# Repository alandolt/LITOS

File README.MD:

# LITOS - **L**ed **I**llumination **T**ool for **O**ptogenetic **S**timulation

**For more information or if you need any help, please contact us at litosforscience[at]outlook.com.**

The **L**ed **I**llumination **T**ool for **O**ptogenetic **S**timulation (**LITOS**) can be used for the stimulation of cells containing an optogenetic system. A commercially available 32x64 RGB LED matrix is used to illuminate cells placed in various microplate formats (6 well up to 96 wells), petri dishes or cell culture flasks. The control unit for the LED matrix is a custom-built printed circuit board (PCB) containing a screen which shows relevant information during the illumination process. 

During LITOS development, we deliberately focused on user-friendliness. LITOS can be ordered pre-built, thus no complicated assembly process is required. Individual stimulation patterns can be first created in a spreadsheet application, like Microsoft Excel, then they are loaded to LITOS over an easy-to-use interface, accessible as a website hosted on the device itself. Thus, no knowledge of a programming language is needed, and the device can even be operated by nontechnical oriented users. 

*LITOS, an easy-to-use system for optogenetic stimulation*

## Why another device for optogenetic stimulation
Optogenetic methods are powerful tools to assess complex signalling pathways with a high spatial-temporal resolution. However, there is a lack of adequate instrumentation to exploit these methods allowing high-throughput automated experiments. While available commercial devices are often too expensive, published solutions requires programming knowledge or have a complicated assembly process. We presents therefore LITOS, a new emerging tool to render optogenetic methods even accessible to labs with a small budget or non-technical user. Thanks to the easy-to-use–interface no knowledge of a programming language is needed, whereas it is still possible to program complex stimulation patterns. Despite being delivered pre-assembled, LITOS remains significantly cheaper than most of the published and commercially available solutions, costing only $ 150. By using a LED matrix as illumination source, even petri-dishes or cell culture flasks can be stimulated in addition to different formats of microtiter plates.

## Features 
- Easy-to-use graphical user interface to change stimulation patterns for optogenetic experiments. No programming knowledge is required. 
- Stimulation patterns are provided as spreadsheet files (MS Excel, LibreOffice Calc)
- It comes pre-assembled. Neither a 3D printer, nor soldering are required before you can start your experiments. 
- Cells can be placed in well plates (96, 48, 24, 12), petri dishes, or cell culture flasks. 
- Very affordable, only about $150 per device. 

## Getting started

To learn more about LITOS, please read our [paper, published 2022 in scientific reports](https://www.nature.com/articles/s41598-022-17312-x), consult our [github wiki](../../wiki) or checkout the [LITOS - First steps](https://youtu.be/o76gi3OUZvs) video.

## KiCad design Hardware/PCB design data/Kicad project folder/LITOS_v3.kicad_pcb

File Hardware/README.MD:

# LITOS Hardware
In case you want to order LITOS directly from a PCB manufacturing service, the folder [*PCB design data*](PCB%20design%20data) contains the needed information (Gerbers file with PCB position file, schematics, and bill of material). Additionally, you can find the raw KiCad PCB layout project under [*LITOS Kicad Rev4.3.zip*](PCB%20design%20data/LITOS%20Kicad%20Rev4.3.zip). 

For the proper alignment of the microtiter plate on the LED matrix the blueprints (for building them with a 3D printer or a CNC machine) for two different masks (one / two microplates) are provided under [*Alignment masks*](Alignment%20masks). The mask for one microplate allows its placement in the middle of the LED matrix, whereas the mask for two plates stocks them horizontally. This allows to stimulate two multiwell plates with one LITOS to further increase through-put. Please note that when using the mask for two plates, the first and last row cannot be illuminated. 

An optional 3D printed case that protects LITOS can be found in the [*3D printed case*](3D%20printed%20case) folder. The case comes in two versions, with or without ventilation holes. Albeit, given that LITOS does not heat up excessively, you can use whichever version you prefer. To minimize overhangs, we recommend you print the case in the orientation it is stored in the .stl file, the open side of the case facing the printer plate. To adjust for under- or overextruding printers, changing the scale of the whole design worked well for us (98%-102%). No support structures were needed with our printer (Creality CR 20 Pro).

<br>

> **Warning** By default, the source code adapted for revision 4 is used during the programming process. When you are still using an older revision 3 board, you can choose the adapted source code for this version by selecting LITOS_Rev2_Rev3 as build environment in PlatformIO. 

*Chose the build environment LITOS_Rev2_Rev3 when you still use an old Rev2 or Rev3 LITOS, else you can directly choose LITOS as build environment.*

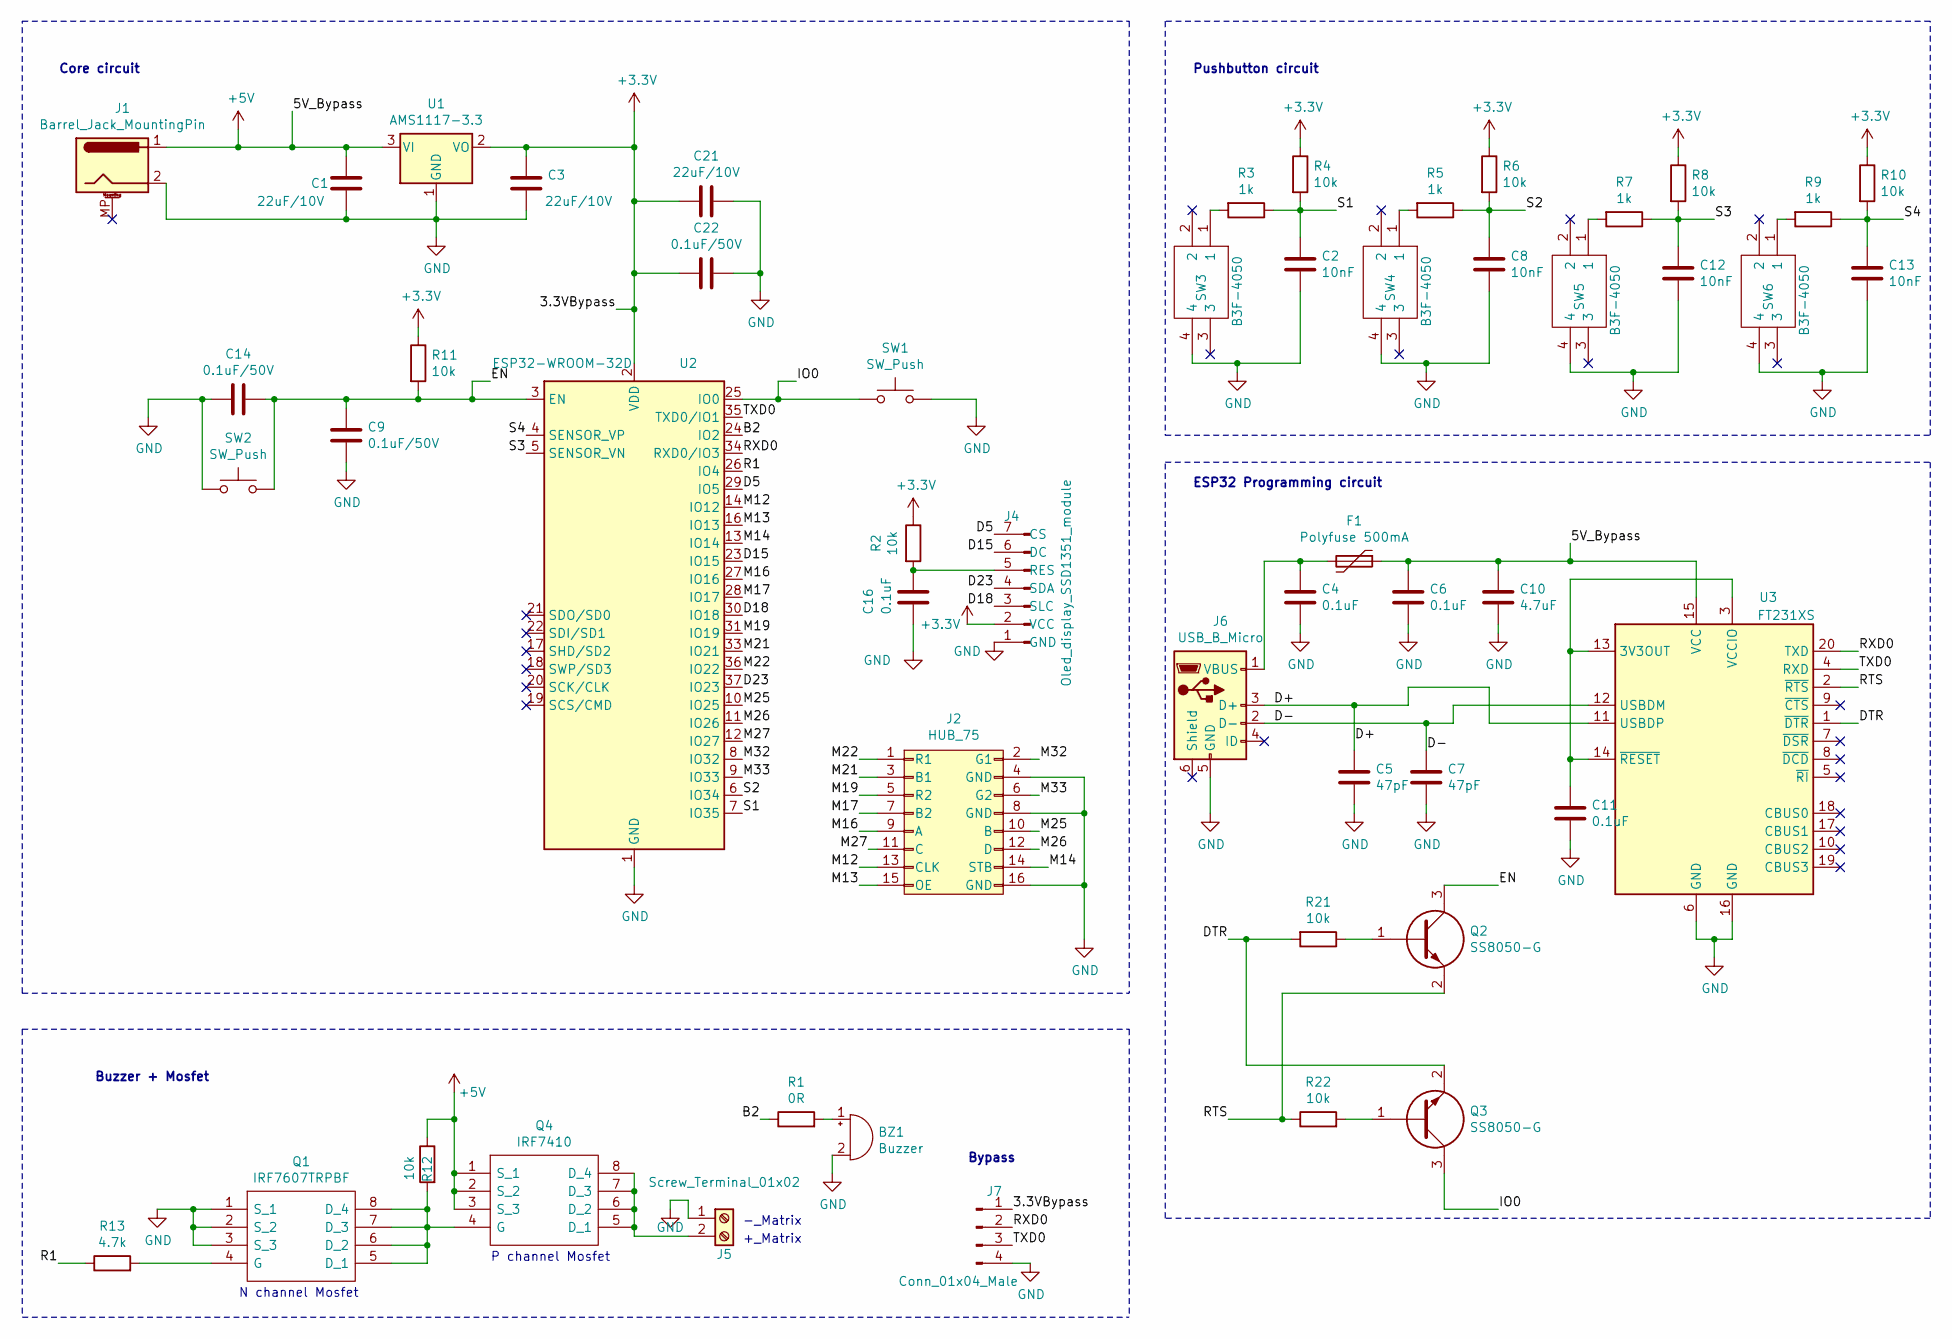
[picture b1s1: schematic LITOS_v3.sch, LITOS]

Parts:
BZ1: Buzzer; CEM-1203_42_
C1, C3, C21: 22uF/10V; C_0603_1608Metric_Pad1.05x0.95mm_HandSolder
C2, C8, C12, C13: 10nF; C_0603_1608Metric_Pad1.05x0.95mm_HandSolder
C4, C6, C11, C16: 0.1uF; C_0603_1608Metric_Pad1.05x0.95mm_HandSolder
C5, C7: 47pF; C_0603_1608Metric_Pad1.05x0.95mm_HandSolder
C9, C14, C22: 0.1uF/50V; C_0603_1608Metric_Pad1.05x0.95mm_HandSolder
C10: 4.7uF; C_0603_1608Metric_Pad1.05x0.95mm_HandSolder
F1: Polyfuse 500mA; Fuse_0805_2012Metric_Pad1.15x1.40mm_HandSolder
J1: Barrel_Jack_MountingPin; CONSOCJ2155
J2: HUB_75; DIPS254W75P254L2764H991Q16N
J4: Oled_display_SSD1351_module; PinSocket_1x07_P2.54mm_Vertical
J5: Screw_Terminal_01x02; SHDR2W100P0X500_1X2_1000X760X1040P
J6: USB_B_Micro; 101181930001LF
J7: Conn_01x04_Male; PinHeader_1x04_P2.54mm_Vertical
Q1: IRF7607TRPBF; SOP65P490X111-8N; Manufacturer_Part_Number IRF7607TRPBF
Q2, Q3: SS8050-G; SOT95P240X115-3N; Mouser Part Number 750-SS8050-G
Q4: IRF7410; SOIC127P600X175-8N
R1: 0R; R_0603_1608Metric_Pad1.05x0.95mm_HandSolder
R2, R4, R6, R8, R10, R11, R12, R21, R22: 10k; R_0603_1608Metric_Pad1.05x0.95mm_HandSolder
R3, R5, R7, R9: 1k; R_0603_1608Metric_Pad1.05x0.95mm_HandSolder
R13: 4.7k; R_0603_1608Metric_Pad1.05x0.95mm_HandSolder
SW1, SW2: SW_Push; PTS647SM70SMTR2LFS
SW3, SW4, SW5, SW6: B3F-4050; B3F-4000; Mouser Part Number 653-B3F-4050
U1: AMS1117-3.3; SOT-223-3_TabPin2
U2: ESP32-WROOM-32D; ESP32-WROOM-32
U3: FT231XS; SSOP-20_3.9x8.7mm_P0.635mm

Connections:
+3V3: C3.1, C21.2, C22.2, J4.2 (VCC), J7.1, R2.1, R4.1, R6.1, R8.1, R10.1, R11.1, U1.2 (VO), U2.2 (VDD)
+5V: C1.1, C6.2, C10.1, F1.1, J1.1, Q4.1 (S_1), Q4.2 (S_2), Q4.3 (S_3), R12.1, U1.3 (VI), U3.15 (VCC)
/B2: R1.1, U2.24 (IO2)
/D5: J4.7 (CS), U2.29 (IO5)
/D15: J4.6 (DC), U2.23 (IO15)
/D18: J4.3 (SLC), U2.30 (IO18)
/D23: J4.4 (SDA), U2.37 (IO23)
/D+: C5.1, J6.3 (D+), U3.11 (USBDP)
/D-: C7.1, J6.2 (D-), U3.12 (USBDM)
/DTR: Q3.2, R21.2, U3.1 (~DTR)
/EN: C9.1, C14.1, Q2.3, R11.2, SW2.2, U2.3 (EN)
/IO0: Q3.3, SW1.1, U2.25 (IO0)
/M12: J2.13 (CLK), U2.14 (IO12)
/M13: J2.15 (OE), U2.16 (IO13)
/M14: J2.14 (STB), U2.13 (IO14)
/M16: J2.9 (A), U2.27 (IO16)
/M17: J2.7 (B2), U2.28 (IO17)
/M19: J2.5 (R2), U2.31 (IO19)
/M21: J2.3 (B1), U2.33 (IO21)
/M22: J2.1 (R1), U2.36 (IO22)
/M25: J2.10 (B), U2.10 (IO25)
/M26: J2.12 (D), U2.11 (IO26)
/M27: J2.11 (C), U2.12 (IO27)
/M32: J2.2 (G1), U2.8 (IO32)
/M33: J2.6 (G2), U2.9 (IO33)
/R1: R13.1, U2.26 (IO4)
/RTS: Q2.2, R22.1, U3.2 (~RTS)
/RXD0: J7.2, U2.34 (RXD0/IO3), U3.20 (TXD)
/S1: C2.2, R3.1, R4.2, U2.7 (IO35)
/S2: C8.2, R5.1, R6.2, U2.6 (IO34)
/S3: C12.2, R7.1, R8.2, U2.5 (SENSOR_VN)
/S4: C13.2, R9.1, R10.2, U2.4 (SENSOR_VP)
/TXD0: J7.3, U2.35 (TXD0/IO1), U3.4 (RXD)
GND: BZ1.2 (+), C1.2, C2.1, C3.2, C4.2, C5.2, C6.1, C7.2, C8.1, C9.2, C10.2, C11.2, C12.1, C13.1, C14.2, C16.2, C21.1, C22.1, J1.2, J2.4 (GND), J2.8 (GND), J2.16 (GND), J4.1 (GND), J5.1, J6.5 (GND), J7.4, Q1.1 (S_1), Q1.2 (S_2), Q1.3 (S_3), SW1.2, SW2.1, SW3.4, SW4.4, SW5.4, SW6.4, U1.1 (GND), U2.1 (GND), U2.15 (GND), U2.38 (GND), U2.39 (GND), U3.6 (GND), U3.16 (GND)
unnamed: BZ1.1 (-), R1.2
unnamed: C4.1, F1.2, J6.1 (VBUS)
unnamed: C11.1, U3.3 (VCCIO), U3.13 (3V3OUT), U3.14 (~RESET)
unnamed: C16.1, J4.5 (RES), R2.2
unnamed: J5.2, Q4.5 (D_1), Q4.6 (D_2), Q4.7 (D_3), Q4.8 (D_4)
unnamed: Q1.4 (G), R13.2
unnamed: Q1.5 (D_1), Q1.6 (D_2), Q1.7 (D_3), Q1.8 (D_4), Q4.4 (G), R12.2
unnamed: Q2.1, R21.1
unnamed: Q3.1, R22.2
unnamed: R3.2, SW3.1
unnamed: R5.2, SW4.1
unnamed: R7.2, SW5.1
unnamed: R9.2, SW6.1

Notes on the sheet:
Pushbutton circuit
Core circuit
+_Matrix
-_Matrix
Buzzer + Mosfet
ESP32 Programming circuit
Bypass
P channel Mosfet
N channel Mosfet

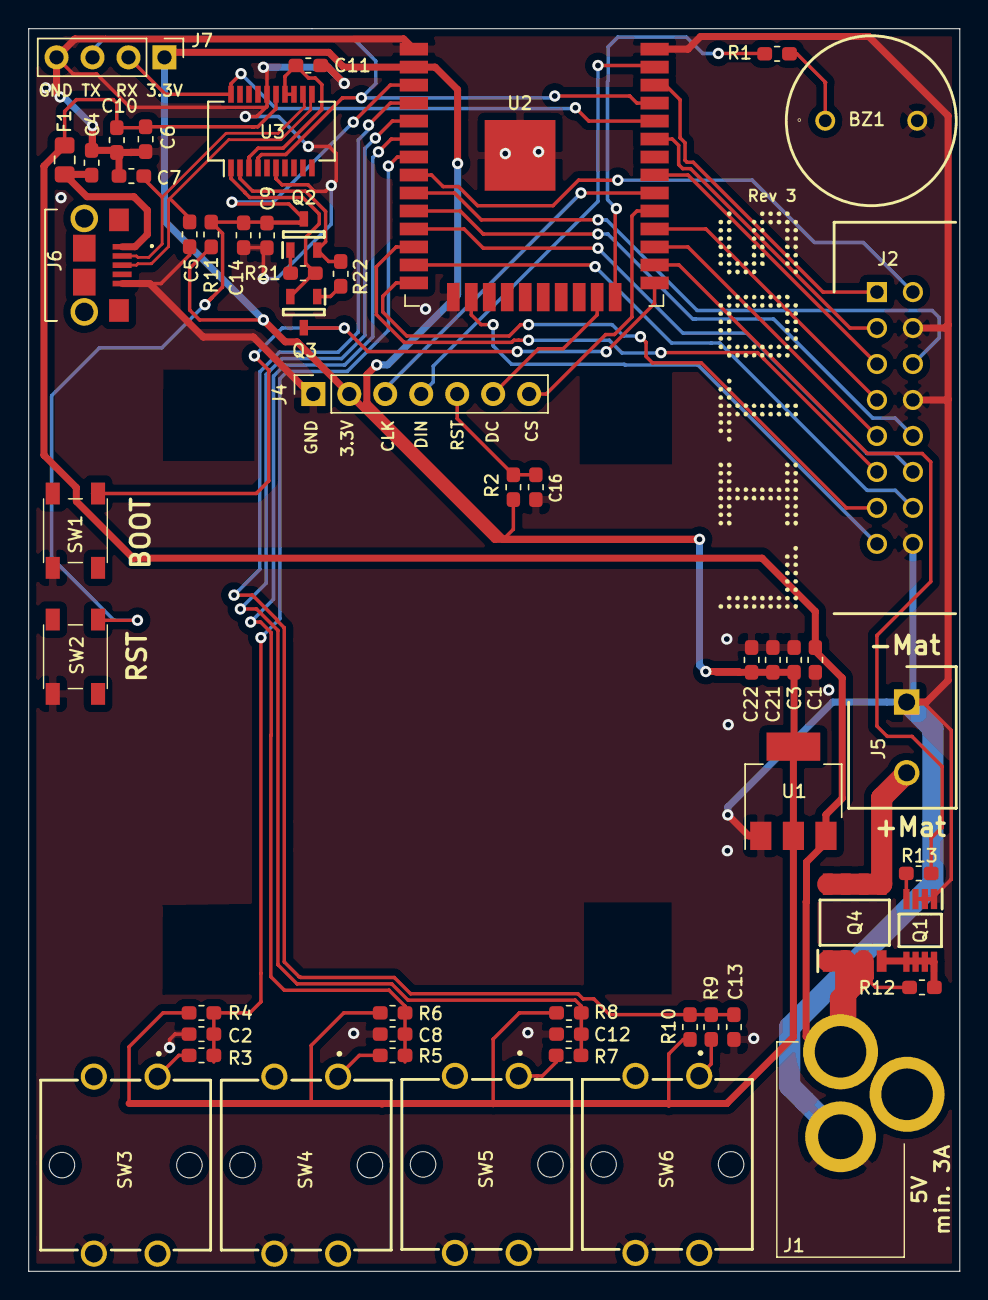
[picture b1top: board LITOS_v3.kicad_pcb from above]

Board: 2 copper layers, 65.8 x 87.8 mm, 53 parts (0 on the bottom side), 47 nets.

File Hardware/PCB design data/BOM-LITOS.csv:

Comment,Designator,Footprint,LCSC,Quantity
0.1uF,"C16,C4,C6",C_0603_1608Metric_Pad1.05x0.95mm_HandSolder,C14663,3
0.1uF/50V,"C14,C22,C9",C_0603_1608Metric_Pad1.05x0.95mm_HandSolder,C14663,3
0R,"R1,R16",R_0603_1608Metric_Pad1.05x0.95mm_HandSolder,C21189,2
100uF,C1,CP_Elec_6.3x5.4,C3001238,1
10k,"R10,R11,R12,R2,R21,R22,R4,R6,R8",R_0603_1608Metric_Pad1.05x0.95mm_HandSolder,C25804,9
10nF,"C12,C13,C2,C8",C_0603_1608Metric_Pad1.05x0.95mm_HandSolder,C57112,4
1k,"R3,R5,R7,R9",R_0603_1608Metric_Pad1.05x0.95mm_HandSolder,C21190,4
22uF/10V,"C21,C3",C_0603_1608Metric_Pad1.05x0.95mm_HandSolder,C59461,2
4.7k,R13,R_0603_1608Metric_Pad1.05x0.95mm_HandSolder,C23162,1
4.7uF,C10,C_0603_1608Metric_Pad1.05x0.95mm_HandSolder,C19666,1
5.11k,"R14,R15",R_0603_1608Metric_Pad1.05x0.95mm_HandSolder,C23186,2
AMS1117-3.3,U1,SOT-223-3_TabPin2,C6186,1
B3F-4050,"SW3,SW4,SW5,SW6",B3F-4050,C86707,4
"BSS138PW,115",Q1,SOT-323-3_L2.2-W1.3-P1.30-LS2.1-BL,C193366,1
Barrel_Jack_MountingPin,J1,DC-005-5A-2.0,C381116,1
Buzzer,BZ1,BUZ-SMD_4P-L8.5-W8.5-TL,C189207,1
CH340C,U3,CH340C,C84681,1
ESP32-WROOM-32E,U2,ESP32-WROOM-32E,C701342,1
HUB_75,J2,B-3000S16P-0110,C132430,1
IRF7416TRPBF,Q4,IRF7416TRPBF,C3000,1
Oled_display_SSD1351_module,J4,PinSocket_1x07_P2.54mm_Vertical,C2886701,1
SS8050-G,"Q2,Q3",SS8050-G,C2150,2
SW_Push,"SW1,SW2",PTS647SN50SMTR2LFS,C2799414,2
Screw_Terminal_01x02,J5,CONN-TH_2P-P7.62_L15.2-W16.7-EX4.2,C496127,1
USB_C_Receptacle_USB2.0,J6,USB-C-SMD_MC-311D,C136423,1
LOGO,G***,logo_litos,,1

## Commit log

2020-02-27 separated, with pushbutton
2020-02-27 working test
2020-02-27 without erease, as else memory overflow
2020-02-27 optimized (pointer), no deleting of vector
2020-02-28 experiment_week_2
2020-02-29 not working
2020-02-29 working with SSD_13XX libary
2020-03-03 working without countdown
2020-03-18 start_18_03
2020-03-21 alter_ansatz_not_working
2020-03-21 working_switch_interpretation
2020-03-21 working_upload
2020-03-22 aufgeteilt in einzelne dateien
2020-03-23 Flickwerk mit webserver
2020-04-02 alles_ohne_display
2020-04-04 same status as first release, felis silvestris
2020-04-04 webserver Basis implementiert
2020-04-20 rename (remove init_)
2020-04-22 two_wellplates now_working
2020-04-24 AP + captive portal (DNS)+ eduroam + improv. save restore
2020-04-25 clean up
2020-04-29 websocket working for two wellplates
2020-04-30 working static
2020-04-30 new_website
2020-05-06 bug fix_websocket crashed in get file list
2020-06-27 comments and compilates again
2020-06-29 zeit_nun_korrekt
2020-07-01 progmem webserver + weitere matrizen
2020-07-01 global_offset_implemented
2020-07-01 delimiter changed to , ;
2020-07-01 weitere farben für Matrix
2020-07-06 1st commit
2020-07-07 ctr/cor text display
2020-07-07 n cycle commit
2020-07-10 verbesserung ,/
2020-07-11 library drin in git
2020-07-11 working matrix sleeping
2020-07-12 small update on refresh rate
2020-07-20 settings page included
2020-07-21 eigene Rechtecke, Kreise
2020-07-22 rect circle nun einstellig, Korr webserver, partition
2020-07-22 1. Fehlerkorrekturen insbesondere buchstaben
2020-07-26 commit_to_change
2020-07-28 1.1.0.alpha: error detection in pattern, website progmem
2020-07-29 bugfix only once+display+file manager
2020-07-30 bufix 6 wellplate display
2020-08-02 hh:mm:ss countdwon + bugfix name
    remaining time is known shown in a hh:mm:ss format instead of seconds
    bugfix of loaded pattern name (was been too long when loaded over website without reset)
2020-08-05 new feature: add custom messages on screen
    New feature allows to create custom messages in pattern file with M_here your message. The start coloumn is used to define the time when the message will appear on the display. With the stimulation t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
    Additionally, update display will now only be called every 100ms instead of every CPU cylce.
2020-08-05 new version numbering system
2020-08-12 modification well_to_x/y; well_col for better fitting
    modification for 48, 24 micro titer plates;
    version 1.2.1
2020-09-07 1.3.0: Outline function
    Implementation of an outline function which marks the outlines of a microplate. Additionally the corner wells can be marked to place the microplate correctly on the LED RGB Matrix. Over the website i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
2020-09-08 1.3.1 Error correction website
2020-09-10 1.3.2 added black keyword
2021-03-15 branch with DMA LED matrix library
    This branch uses the DMA LED matrix from
    https://github.com/mrfaptastic/ESP32-RGB64x32MatrixPanel-I2S-DMA/
    It uses DMA memory instead of heap allocation.
    In theory it uses less CPU.
    As the underlaying API is different (Adafruit GFX instead of smartmatrix), all function calls manipulating the drawn forms in wellplate.cpp and matrix.cpp were changed. Additionally, as the radius is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
2021-05-13 Bugfix for FM61126A branch, namely removal of swap.layer method, adaptation of size of illumination size + adaptation to other API
2021-05-13 Addition of Website files and images for wiki
2021-07-27 Housekeeping: Addition of README.MD and manual
2021-07-28 Addition of wiki images and change in readme
2021-07-28 image added
2022-01-27 change in gitignore
2022-02-01 Addition of masks for 3D printer
2022-02-02 Move everything to software related to software folder
2022-02-06 Adding Readme for Software
2022-02-06 readme software width
2022-02-06 readme correct image size
2022-02-13 Addition of PCB schematics
2022-02-13 Cleanup of old ToDo and old user manual
2022-02-22 spelling
2022-03-17 added example patterns
2022-03-17 changed demo files
2022-03-17 add new demo file
2022-03-17 move files to folder example patterns
2022-04-07 Pre-release of hardware revision 4 of LITOS PCB
    - USB flashing error present in rev 3 got fixed
    - Software mostly interchangable between rev 3 and 4.
    - PCB revision gets currently tested
    - For more information, see Redme in hardware folder.
2022-04-16 Bugfix for PCB Pre-release Rev 4
    - Depending on the micro USB, you have chosen for the assembly, it is possible that the micro USB connector flange is placed on top of the board, instead being feely besides the board. By placing the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
2022-05-13 Update Readme to relative links
2022-05-13 Fixed external version dependencies Previously compillaton did not work due to breaking change in esp async webserver dependencies. Thus external dependencies were changed to last known working versi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
2022-05-13 Compillation did not work anymore on new esp32 core due to ESP32 Async webserver library.
    Fixed by taken this library directly from git repository instead of platformio repo
2022-05-14 Adding short tutorial video to wiki
    video was created by Thomas Höhener for the InSiDE Workshop: Optogenetics, held on March 10th
2022-05-18 Change to espressif32 3.5.0 as rebootloop when flashing with espressif32 4.2.0 framework
2022-05-18 Correction of button mapping
    Rev4 uses other schematics than Rev2. Therefore, the button mapping had to be adapted:
    Red Button = GPIPO 36 = Sens VP
    Yellow Button = GPIO 39 = Sens VN
    Blue Button = GPIO 34 = VDet1
    Green Button = GPIO 35 = VDet2
2022-05-18 Increase timeout before display init
    Previously there were problems with display init, so that a reset needed to be performed before something was shown on the screen. By extending the timeout u8ntil the display was initialised, this pr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
2022-05-19 Adapt Platformio.ini and code to be able to compile LITOS source code for both board revisions, Rev 2 and Rev4.
    The board revisions 2 and 4 are distinguished by different button mappings. Further, some of the Rev2 boards had problems with a spontanous triggering of the quit (green) button. Thus, the exit of th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
    Pin definitions for the baords can be found in button.h
2022-05-19 LITOS Release 2.0 with hardware revision 4
    Compared to the prerelease of revision 4, C5 had been removed. It seems that the capacitors attached to the buttons of RST and BOOT lock the ESP32 into the bootloader when doing a cold start as both 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
    Further the board was shortened by 1 mm, as the linked micro-USB connector could not be soldered flat on the board, as some overhang was needed for the micro-USB connector.
    To ensure compatibility with LITOS Rev2 and Rev3, we added a LITOS_Rev2_Rev3 build
2022-05-24 Bugfix LED x/y parsing
    It is now possible agin to illuminate individual LEDs by using the LED_x_y what command.
2022-05-24 Bugfix Rectangle + Circle parsing
2022-05-25 Update Software Readme, fix broken link
2022-05-25 add more detailled flashing instructions in wiki
2022-05-30 Update README.MD with 3d printer information
    - Added details for 3d printing process
    - Changed to new warning block-quote (github.com/github/feedback/discussions/16925)
2022-05-30 Figure that shows 3d prints
    - solid model
    - model with vents
    - photo of design with vents
2022-05-30 added image of 3d printed cases
2022-05-30 added 3d printing details (#1)
    * Update README.MD with 3d printer information
    - Added details for 3d printing process
    - Changed to new warning block-quote (github.com/github/feedback/discussions/16925)
    * Figure that shows 3d prints
    - solid model
    - model with vents
2022-06-18 Bugfix: alignment, messages, debug output
    - Previously the alignment functions drew a filled rectangle, now again only the contours are drawn.
    - Debug messages are not shown anymore on the serial interface. They can be enabled by settings DEBUG_SERIAL_OUT as preprocessor variable (see platformio.ini).
    - Messages are previously shown up to 10 minutes. This time had been reduced to 1 min, so that multiple messages can be shown.
2022-06-27 Add MIT license
2022-07-23 Bugfix parsing .csv + update gitignore
    - Parsing .csv with ; as delimiter should now work again.
    - Update gitignore to include rules for node.js
2022-10-24 Increase temporal resolution
    - Introduction of p unit in csv which stands for ms.
2022-11-29 Add link to scientific reports paper
2022-12-18 compatibility with Rev 4.3
2022-12-30 Bugfix website
    - compilation of website works again.
    - Removal of old zopfli node module (not used anymore).
2022-12-30 Bugfix: change AP name
    - It is now possible again to change the access point name.
    - The default platformio environement had been changed to the new hardware revision (Rev 4.3, using USB-C).
2023-03-01 update how to get LITOS
2023-03-20 Working captive portal
2023-03-22 1. Implentierung neuer Algorithmus, arbeitet mit Vergleich statt Modulo
2023-03-22 working without blocks
2023-03-23 scheint zu funktionieren, aber noch hardcoded Werte für block
2023-03-23 Working with new setup block
2023-03-23 Example with blocks + code cleanup
2023-03-23 Variante: repeat every does not take into account the stimulation time
2023-03-23 Other variant:
    - Here stim time does not count to repeat every
2023-03-24 Better demo file
2023-05-05 Bugfix: Decrease upload speed to speed of the master branch
2023-06-22 Rename enviroments due to new platformio naming policies
2023-06-22 Rename platformio environement due to new naming policies
2023-10-08 Addition of adapted demo code + change message block
2024-05-05 Update Dependencies:
    - Update some library dependencies which were not available anymore on platformio libarary list, hence compilation did not work anymore.
2025-11-27 Bugfix: Locking ESPAsync WebServer to required git commit
    - Non locking lead to compillation version in recent versions.
2026-01-29 Adding PCB Hardware Revision 4.3
    - USB-C instead of microUSB connection
    - Update MOSFET circuit, as original MOSFET was out of production
    - Smaller Fixes in hardware design
